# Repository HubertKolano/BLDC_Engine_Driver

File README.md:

# Praca_inzynierska
Sterownik procesowy silnika BLDC z funkcjonalnością IoT / BLDC engine process controller with IoT functionality

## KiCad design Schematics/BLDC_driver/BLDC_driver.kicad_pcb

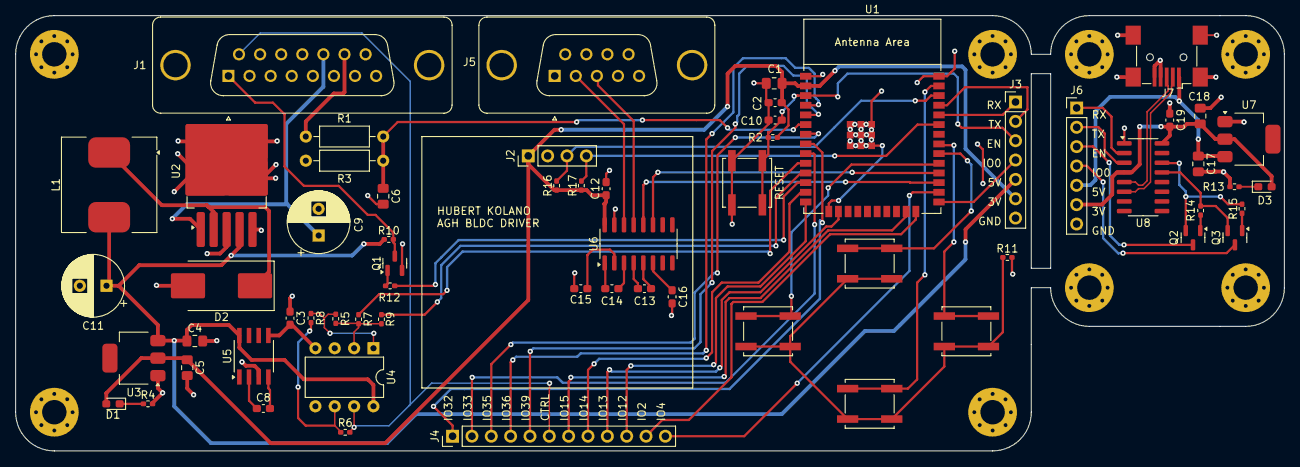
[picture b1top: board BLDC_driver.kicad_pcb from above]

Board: 2 copper layers, 166.6 x 57.2 mm, 70 parts (0 on the bottom side), 66 nets.

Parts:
C1, C4, C5, C6, C17, C18: 22u; C_0805_2012Metric_Pad1.18x1.45mm_HandSolder
C2, C3, C8, C10, C12, C13, C14, C15, C16, C19: 0.1u; C_0603_1608Metric_Pad1.08x0.95mm_HandSolder
C9, C11: 220u/35v; CP_Radial_D8.0mm_P3.50mm
D1, D3: RED; D_0603_1608Metric_Pad1.05x0.95mm_HandSolder
D2: B320; D_SMC_Handsoldering
H1, H2, H3, H4, H5, H6, H7, H8: MountingHole; MountingHole_3.2mm_M3_Pad_Via
J1: DA15_Plug_MountingHoles; DSUB-15_Female_Vertical_P2.77x2.84mm_MountingHoles
J2: Display connectors; PinHeader_1x04_P2.54mm_Vertical
J3: Programmer IO; PinHeader_1x07_P2.54mm_Vertical
J4: unused pins; PinHeader_1x12_P2.54mm_Vertical
J5: DE9_Receptacle_MountingHoles; DSUB-9_Female_Vertical_P2.77x2.84mm_MountingHoles
J6: Conn_01x07_Pin; PinHeader_1x07_P2.54mm_Vertical
J7: USB_B_Micro; USB_Mini-B_Wuerth_65100516121_Horizontal
L1: 33u; L_Coilcraft_MSS1278T-XXX
Q1, Q2, Q3: 2N7002; SOT-23
R1: 10k; R_Axial_DIN0207_L6.3mm_D2.5mm_P10.16mm_Horizontal
R2, R4, R6, R7, R8, R9, R11, R12, R13, R14, R15: 10k; R_0402_1005Metric_Pad0.72x0.64mm_HandSolder
R3: 1k6; R_Axial_DIN0207_L6.3mm_D2.5mm_P10.16mm_Horizontal
R5: 7k5; R_0402_1005Metric_Pad0.72x0.64mm_HandSolder
R10: 100; R_0402_1005Metric_Pad0.72x0.64mm_HandSolder
R16, R17: 3k3; R_0402_1005Metric_Pad0.72x0.64mm_HandSolder
RESET: SW_Push; SW_Push_1P1T_NO_CK_KSC6xxJ22
SW2, SW3, SW4, SW5: SW_Push; SW_Push_1P1T_NO_CK_KSC6xxJ22
U1: ESP32-WROOM-E; ESP32-WROOM-32E
U2: LM2596S-5; TO-263-5_TabPin3
U3, U7: AMS1117-3.3; SOT-223
U4: LM358; DIP-8_W7.62mm
U5: ICL7660; PowerIntegrations_SO-8
U6: MAX3232; SOP-16_3.9x9.9mm_P1.27mm
U8: CH340C; SOIC-16_3.9x9.9mm_P1.27mm

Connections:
+3.3V: C1.1, C2.1, C5.1, C12.1, D1.2 (A), J2.1, J3.6, R2.1, R16.1, R17.1, U1.2 (3V3), U3.2 (VO), U6.16 (VCC)
+5V: C4.1, C11.1, J3.5, L1.2, R10.1, U2.4 (FB), U3.3 (VI), U4.8 (V+), U5.8 (V+)
+24V: C9.1, J1.13, U2.1 (VIN)
-5V: C3.2, U4.4 (V-), U5.5 (VOUT)
/+3.3V USB: C18.1, C19.1, D3.2 (A), J6.6, U7.2 (VO), U8.4 (V3), U8.16 (VCC)
/+5V USB: C17.1, J6.5, J7.1 (VBUS), U7.3 (VI)
/CTRL: J1.9, J4.6, R6.2, U4.7
/D+: J7.3 (D+), U8.5 (UD+)
/D-: J7.2 (D-), U8.6 (UD-)
/DAC1: R7.1, U1.10 (DAC_1/ADC2_CH8/GPIO25)
/DAC2: R9.1, U1.11 (DAC_2/ADC2_CH9/GPIO26)
/DIR: J1.1, Q1.3 (D), R10.2
/DIR control: R12.1, U1.12 (ADC2_CH7/GPIO27)
/DTR: Q3.2 (S), R14.2, U8.13 (~DTR)
/EN: C10.1, J3.3, R2.2, RESET.2, U1.3 (EN/CHIP_PU)
/EN USB: J6.3, Q2.3 (D)
/GPIO0: J3.4, U1.25 (GPIO0/BOOT/ADC2_CH1)
/GPIO0 USB: J6.4, Q3.3 (D)
/IO2: J4.11, U1.24 (ADC2_CH2/GPIO2)
/IO4: J4.12, U1.26 (ADC2_CH0/GPIO4)
/IO12: J4.10, U1.14 (MTDI/GPIO12/ADC2_CH5)
/IO13: J4.9, U1.16 (MTCK/GPIO13/ADC2_CH4)
/IO14: J4.8, U1.13 (MTMS/GPIO14/ADC2_CH6)
/IO15: J4.7, U1.23 (MTDO/GPIO15/ADC2_CH3)
/IO32: J4.1, U1.8 (32K_XP/GPIO32/ADC1_CH4)
/IO33: J4.2, U1.9 (32K_XN/GPIO33/ADC1_CH5)
/IO35: J4.3, U1.7 (GPIO35/ADC1_CH7)
/IO36: J4.4, U1.4 (SENSOR_VP/GPIO36/ADC1_CH0)
/IO39: J4.5, U1.5 (SENSOR_VN/GPIO39/ADC1_CH3)
/R1IN: J5.3, U6.13 (R1IN)
/RPM: J1.14, R1.1
/RPM DIVIDED: C6.1, R1.2, R3.1, U1.6 (GPIO34/ADC1_CH6)
/RTS: Q2.2 (S), R15.2, U8.14 (~RTS)
/SCL: J2.3, R16.2, U1.36 (GPIO22)
/SDA: J2.4, R17.2, U1.33 (GPIO21)
/SW1: SW2.1, U1.30 (GPIO18)
/SW2: SW3.1, U1.37 (GPIO23)
/SW3: SW4.1, U1.31 (GPIO19)
/SW4: SW5.1, U1.29 (GPIO5)
/T1OUT: J5.2, U6.14 (T1OUT)
/U0RX: J3.1, U1.34 (U0RXD/GPIO3)
/U0RX USB: J6.1, U8.2 (TXD)
/U0TX: J3.2, U1.35 (U0TXD/GPIO1)
/U0TX USB: J6.2, U8.3 (RXD)
/U2RX: U1.27 (GPIO16), U6.12 (R1OUT)
/U2TX: U1.28 (GPIO17), U6.11 (T1IN)
GND: C1.2, C2.2, C3.1, C4.2, C5.2, C6.2, C9.2, C10.2, C11.2, C12.2, C15.2, C16.2, D2.2 (A), H1.1, H2.1, H3.1, H4.1, J1.0 (PAD), J1.12, J2.2, J3.7, J5.0 (PAD), J5.5, Q1.2 (S), R3.2, R4.2, R11.2, RESET.1, U1.1 (GND), U1.15 (GND), U1.38 (GND), U1.39 (GND_THERMAL), U2.3 (GND), U2.5 (~ON/OFF), U3.1 (GND), U4.3 (+), U4.5 (+), U5.3 (GND), U6.15 (GND)
GND1: C17.2, C18.2, C19.2, H5.1, H6.1, H7.1, H8.1, J6.7, J7.4 (ID), J7.5 (GND), J7.6 (Shield), R13.2, U7.1 (GND), U8.1 (GND)
unnamed: D1.1 (K), R4.1
unnamed: D2.1 (K), L1.1, U2.2 (OUT)
unnamed: D3.1 (K), R13.1
unnamed: Q1.1 (G), R12.2
unnamed: Q2.1 (G), R14.1
unnamed: Q3.1 (G), R15.1
unnamed: R5.2, R8.1, U4.1
unnamed: R11.1, SW2.2, SW3.2, SW4.2, SW5.2
unnamed: R5.1, R7.2, R9.2, U4.2 (-)
unnamed: R6.1, R8.2, U4.6 (-)
unnamed: C8.1, U5.2 (CAP+)
unnamed: C8.2, U5.4 (CAP-)
unnamed: C14.1, U6.1 (C1+)
unnamed: C14.2, U6.3 (C1-)
unnamed: C13.1, U6.4 (C2+)
unnamed: C13.2, U6.5 (C2-)
unnamed: C15.1, U6.2 (VS+)
unnamed: C16.1, U6.6 (VS-)

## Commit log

2024-06-27 KiCad schematic added
    First iteration without DAC support for BLDC driver
2024-07-23 Further Schematic Progress
    Added some components, assigned most of the footprints, one more commit. All basic functionalities considered in the schematic.
2024-07-28 Finished design
    Generated gerber files, upgraded to KiCAD 8.0.7 this is final design (hopefully)
2024-07-29 Fixed incorrect diode
    Switching regulator diode changed to zener from shottky (same footprint)
2024-08-24 First draft of code
    Added oled and dac functionality
2024-08-25 Button functionality
    Added buttons service with more flexible and clean code
2024-08-25 Further project development
    Second core and testing functionality added
2024-08-26 Added second core functionality and testing code
2024-08-29 Skończono opis hardware
    Napisano całą część hardwere'ową pracy, do tego poprawiono element z wzmacniaczem na schemacie, żeby tylko jeszcze przyszedł na czas.
2024-09-02 Testing board code complete, document had first review
2024-09-03 Learned about PID and implemented it
2024-09-05 95% zrobione
    Poprawić UART w programie, dokończyć parę podrozdziałów
2024-09-05 FIRST FULL DRAFT
    Wysłano do promotora kompletną prace inzynierską
2024-09-06 Sent to APD
    This shall finalize the project.
2024-09-11 Dodano pdf do druku
    Przygotowano poprawny pdf do druku, oraz rozpoczęto prace nad prezką.
2024-09-16 Utworzenie prezentacji na obronę pracy.
2024-09-19 Added working SCPI commands on rs232
2024-11-04 Update LICENSE
2024-11-04 Reorganized files
2024-11-04 Updated gitignore
